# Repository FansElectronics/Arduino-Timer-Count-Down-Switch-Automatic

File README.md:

# Arduino-Timer-Count-Down-Switch-Automatic
Project Timer Counter Down for Switch OFF using Arduino Nano

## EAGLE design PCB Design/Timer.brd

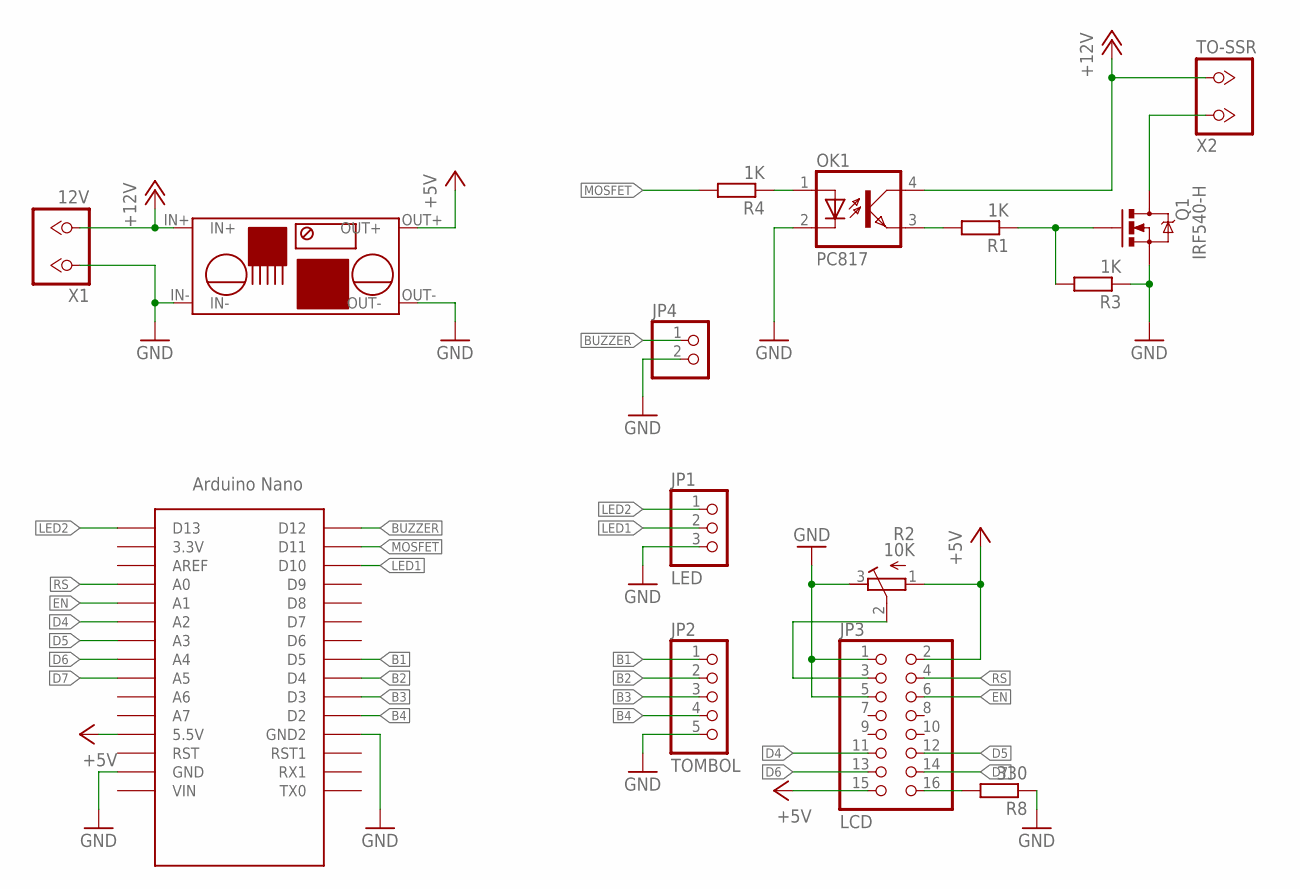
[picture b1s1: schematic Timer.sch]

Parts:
JP1: LED; 1X03
JP2: TOMBOL; 1X05
JP3: LCD; 2X08
JP4: PINHD-1X2; 1X02
MOD1: LM2576
OK1: PC817; DIL04
Q1: IRF540-H; TO-220H
R1, R3, R4: 1K; 0207/7
R2: 10K; RTRIM3339
R8: 330; 0207/7
U$1: NANO
X1: 12V; KL2
X2: TO-SSR; KL2

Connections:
+5V: JP3.2, JP3.15, MOD1.OUT+, R2.1 (A), U$1.5V (5.5V)
+12V: MOD1.IN+, OK1.4 (COL), X1.2, X2.2
B1: JP2.1, U$1.D5
B2: JP2.2, U$1.D4
B3: JP2.3, U$1.D3
B4: JP2.4, U$1.D2
BUZZER: JP4.1, U$1.D12
D4: JP3.11, U$1.A2
D5: JP3.12, U$1.A3
D6: JP3.13, U$1.A4
D7: JP3.14, U$1.A5
EN: JP3.6, U$1.A1
GND: JP1.3, JP2.5, JP3.1, JP3.5, JP4.2, MOD1.IN-, MOD1.OUT-, OK1.2 (C), Q1.3 (S), R2.3 (E), R3.1, R8.1, U$1.GND, U$1.GND1 (GND2), X1.1
LED1: JP1.2, U$1.D10
LED2: JP1.1, U$1.D13
MOSFET: R4.2, U$1.D11
unnamed: Q1.1 (G), R1.1, R3.2
unnamed: OK1.3 (EMIT), R1.2
unnamed: JP3.16, R8.2
unnamed: Q1.2 (D), X2.1
unnamed: OK1.1 (A), R4.1
unnamed: JP3.3, R2.2 (S)
RS: JP3.4, U$1.A0

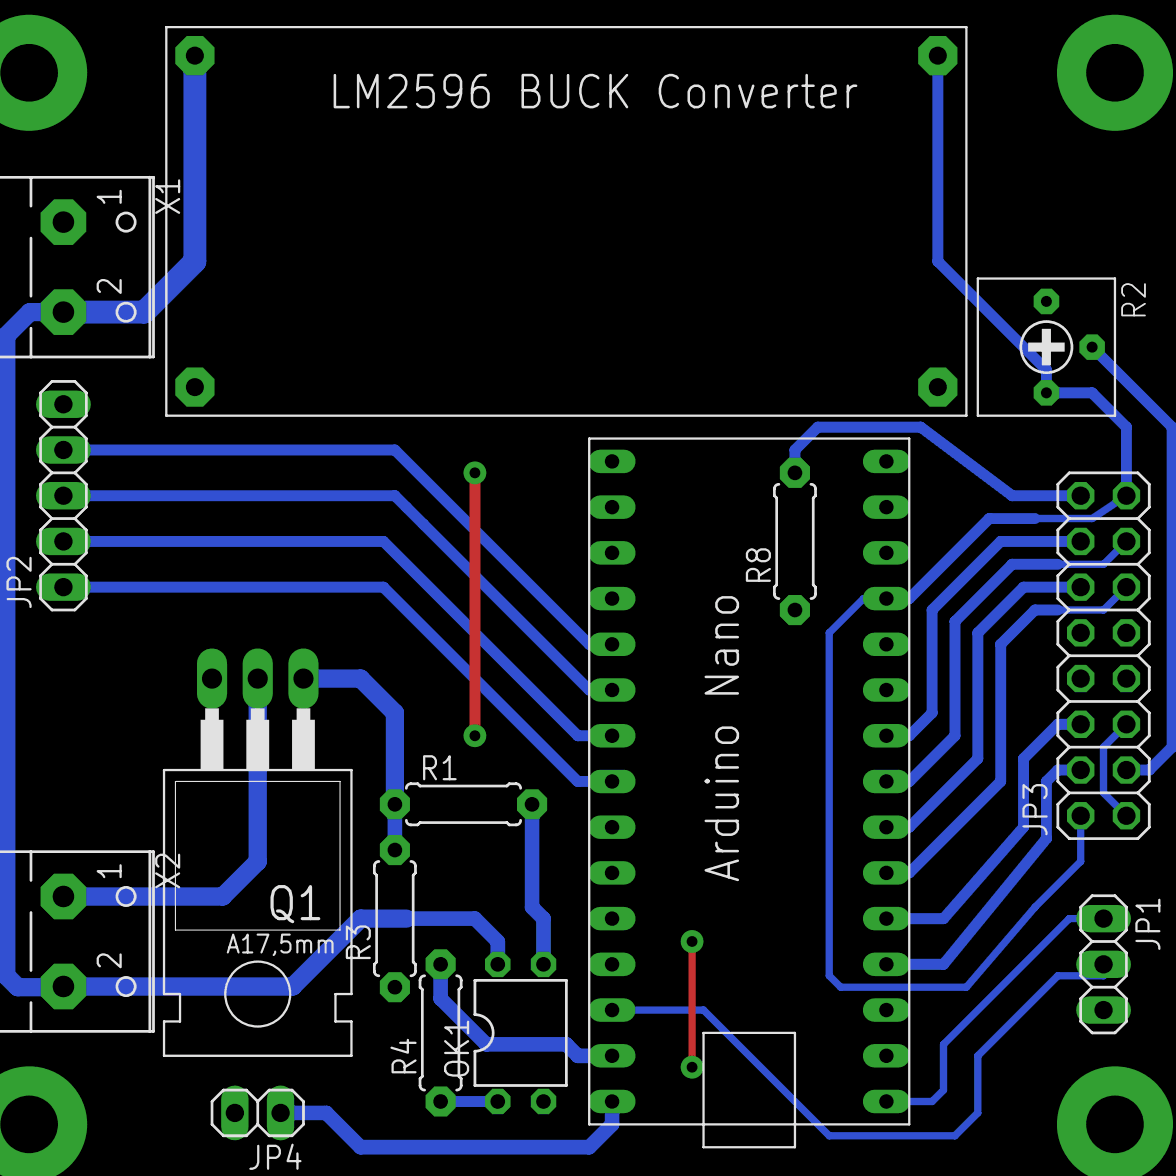
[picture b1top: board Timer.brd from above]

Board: 2 copper layers, 15 parts (0 on the bottom side), 23 nets.

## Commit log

2019-07-18 Fixing Design
